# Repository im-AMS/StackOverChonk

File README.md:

# References

- [custom ergogen-footprints](https://github.com/ceoloide/ergogen-footprints)
- [3d models to view in kicad](https://github.com/joe-scotto/scottokeebs/tree/main/Extras/ScottoKicad)
- [josukey](https://github.com/Narkoleptika/josukey)
- [avocado](https://github.com/auryn31/avocado)
- [supermini pinout specs](https://docs.nordicsemi.com/bundle/ps_nrf52840/page/pin.html)
- [Arduino Pro Micro Pinout](https://cdn.sparkfun.com/assets/9/c/3/c/4/523a1765757b7f5c6e8b4567.png)
- [ergogen configs from Corney-island](https://github.com/ceoloide/corney-island/blob/main/ergogen/config.yaml)
- [svg to points](https://shinao.github.io/PathToPoints/)

# Renders

# Personal Notes and Todos
For RGB Underglow, ZMK docs recomments using high speed gpio pins. refer to the attached pinout specs above.

Try to reserve pins like so (pins in arduino format)
- D2 & D3 for I2C - for Displays
- D6 for high speed comms like RGB underglow, because docs is also using it
- D14, D15, D16 - SPI - idk what i might use this for, just leave em blank

can the battery be connected to RAW for charging or do i have to connect it to top two pins

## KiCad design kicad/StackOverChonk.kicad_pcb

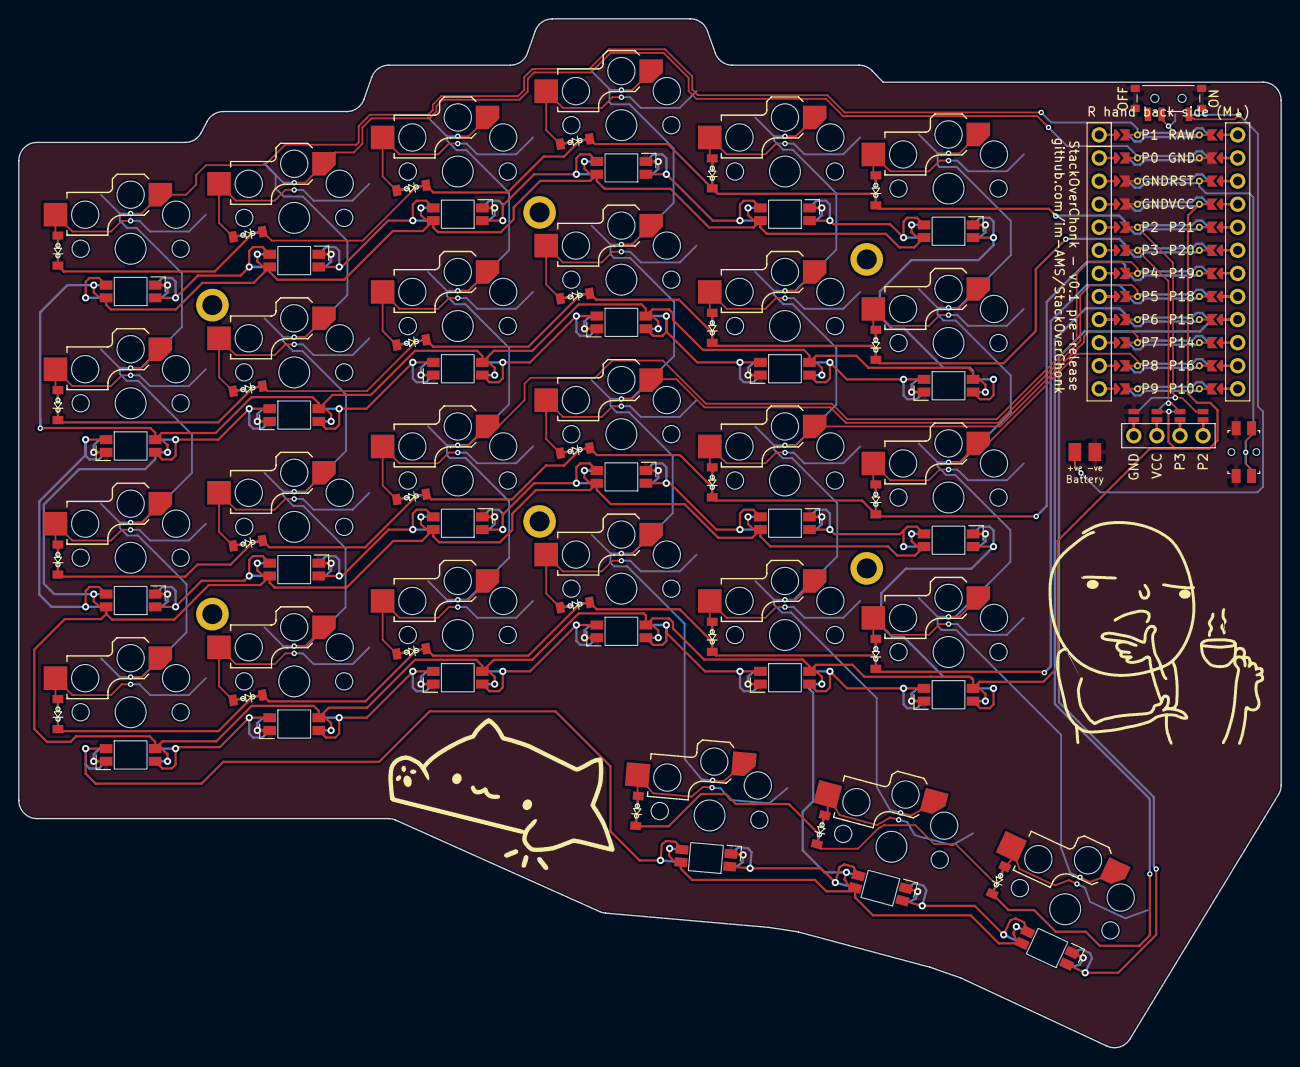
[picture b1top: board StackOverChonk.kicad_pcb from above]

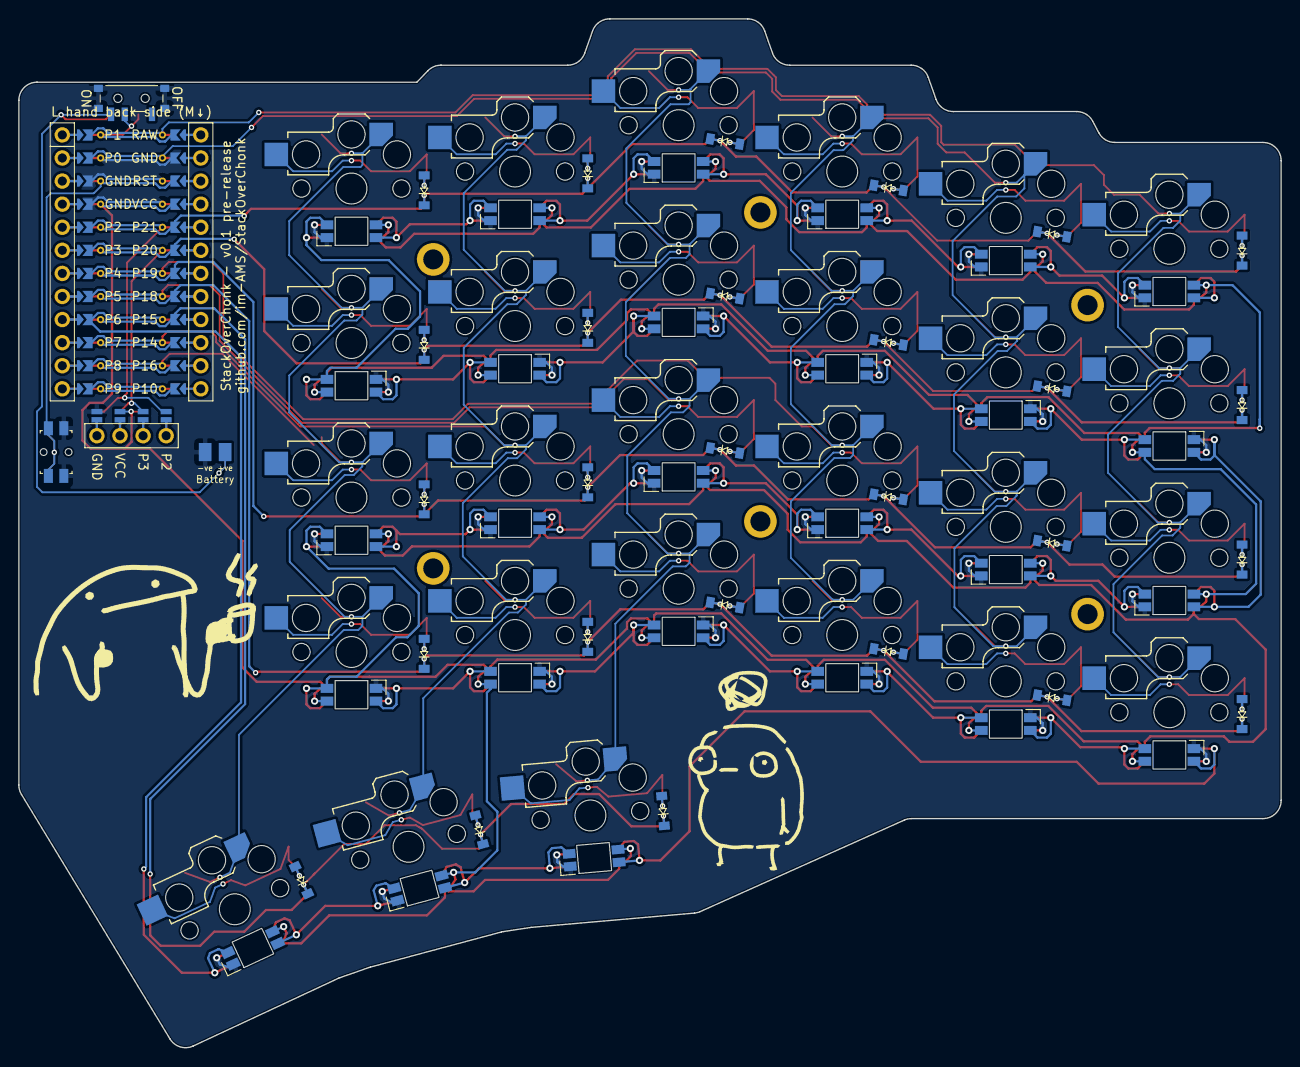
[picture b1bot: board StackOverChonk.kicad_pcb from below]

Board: 2 copper layers, 138.9 x 113.2 mm, 93 parts (35 on the bottom side), 76 nets.

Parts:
BT1, BT2: Battery_pads
D1, D2, D3, D4, D5, D6, D7, D8, D9, D10, D11, D12, D13, D14, D15, D16, D17, D18, D19, D20, D21, D22, D23, D24, D25, D26, D27: diode_tht_sod123
DISP1: display_ssd1306
H1, H2, H3, H4, H5, H6: mounting_hole_plated
LED1, LED2, LED3, LED4, LED5, LED6, LED7, LED8, LED9, LED10, LED11, LED12, LED13, LED14, LED15, LED16, LED17, LED18, LED19, LED20, LED21, LED22, LED23, LED24, LED25, LED26, LED27: led_SK6812mini-e (per-key, reversible)
MCU1: mcu_supermini_nrf52840
PWR1: power_switch_smd_side
RST1: reset_switch_smd_side
S1, S2, S3, S4, S5, S6, S7, S8, S9, S10, S11, S12, S13, S14, S15, S16, S17, S18, S19, S20, S21, S22, S23, S24, S25, S26, S27: switch_choc_v1_v2

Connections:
DISP1_1: DISP1.1, DISP1.10, DISP1.23
DISP1_2: DISP1.2, DISP1.11, DISP1.22
DISP1_3: DISP1.3, DISP1.12, DISP1.21
DISP1_4: DISP1.4, DISP1.13, DISP1.20
GND: BT1.2, BT2.2, DISP1.14, DISP1.24, LED1.3, LED2.3, LED3.3, LED4.3, LED5.3, LED6.3, LED7.3, LED8.3, LED9.3, LED10.3, LED11.3, LED12.3, LED13.3, LED14.3, LED15.3, LED16.3, LED17.3, LED18.3, LED19.3, LED20.3, LED21.3, LED22.3, LED23.3, LED24.3, LED25.3, LED26.3, LED27.3, MCU1.102, MCU1.121, MCU1.122, PWR1.STAB1, PWR1.STAB2, PWR1.STAB3, PWR1.STAB4, RST1.2, RST1.4
LED_1: LED26.4, LED27.2
LED_2: LED25.4, LED26.2
LED_3: LED1.4, LED25.2
LED_4: LED1.2, LED3.4
LED_5: LED3.2, LED5.4
LED_6: LED5.2, LED7.4
LED_7: LED7.2, LED9.4
LED_8: LED9.2, LED11.4
LED_9: LED11.2, LED23.4
LED_10: LED21.4, LED23.2
LED_11: LED19.4, LED21.2
LED_12: LED17.4, LED19.2
LED_13: LED15.4, LED17.2
LED_14: LED13.4, LED15.2
LED_15: LED2.4, LED13.2
LED_16: LED2.2, LED4.4
LED_17: LED4.2, LED6.4
LED_18: LED6.2, LED8.4
LED_19: LED8.2, LED10.4
LED_20: LED10.2, LED12.4
LED_21: LED12.2, LED24.4
LED_22: LED22.4, LED24.2
LED_23: LED20.4, LED22.2
LED_24: LED18.4, LED20.2
LED_25: LED16.4, LED18.2
LED_26: LED14.4, LED16.2
P0: MCU1.123, S5.1, S6.1, S7.1, S8.1
P1: MCU1.124, S1.1, S2.1, S3.1, S4.1
P2: DISP1.17, DISP1.27, MCU1.120
P3: DISP1.16, DISP1.26, MCU1.119
P4: MCU1.118, S9.1, S10.1, S11.1, S12.1
P5: MCU1.117, S13.1, S14.1, S15.1, S16.1, S25.1
P6: LED27.4, MCU1.116
P7: MCU1.115, S17.1, S18.1, S19.1, S20.1, S26.1
P8: MCU1.114, S21.1, S22.1, S23.1, S24.1, S27.1
P15: D25.1, D26.1, D27.1, MCU1.109
P18: D1.1, D5.1, D9.1, D13.1, D17.1, D21.1, MCU1.108
P19: D2.1, D6.1, D10.1, D14.1, D18.1, D22.1, MCU1.107
P20: D3.1, D7.1, D11.1, D15.1, D19.1, D23.1, MCU1.106
P21: D4.1, D8.1, D12.1, D16.1, D20.1, D24.1, MCU1.105
RAW: MCU1.101, PWR1.2
RST: MCU1.103, RST1.1, RST1.3
VCC: DISP1.15, DISP1.25, LED1.1, LED2.1, LED3.1, LED4.1, LED5.1, LED6.1, LED7.1, LED8.1, LED9.1, LED10.1, LED11.1, LED12.1, LED13.1, LED14.1, LED15.1, LED16.1, LED17.1, LED18.1, LED19.1, LED20.1, LED21.1, LED22.1, LED23.1, LED24.1, LED25.1, LED26.1, LED27.1, MCU1.104
matrix_index_down: D17.2, S17.2
matrix_index_home: D18.2, S18.2
matrix_index_num: D20.2, S20.2
matrix_index_up: D19.2, S19.2
matrix_inner_down: D21.2, S21.2
matrix_inner_home: D22.2, S22.2
matrix_inner_num: D24.2, S24.2
matrix_inner_up: D23.2, S23.2
matrix_middle_down: D13.2, S13.2
matrix_middle_home: D14.2, S14.2
matrix_middle_num: D16.2, S16.2
matrix_middle_up: D15.2, S15.2
matrix_outer_down: D1.2, S1.2
matrix_outer_home: D2.2, S2.2
matrix_outer_num: D4.2, S4.2
matrix_outer_up: D3.2, S3.2
matrix_pinky_down: D5.2, S5.2
matrix_pinky_home: D6.2, S6.2
matrix_pinky_num: D8.2, S8.2
matrix_pinky_up: D7.2, S7.2
matrix_ring_down: D9.2, S9.2
matrix_ring_home: D10.2, S10.2
matrix_ring_num: D12.2, S12.2
matrix_ring_up: D11.2, S11.2
pos: BT1.1, BT2.1, PWR1.1, PWR1.3
thumbs_col1_cluster: D25.2, S25.2
thumbs_col2_cluster: D26.2, S26.2
thumbs_col3_cluster: D27.2, S27.2

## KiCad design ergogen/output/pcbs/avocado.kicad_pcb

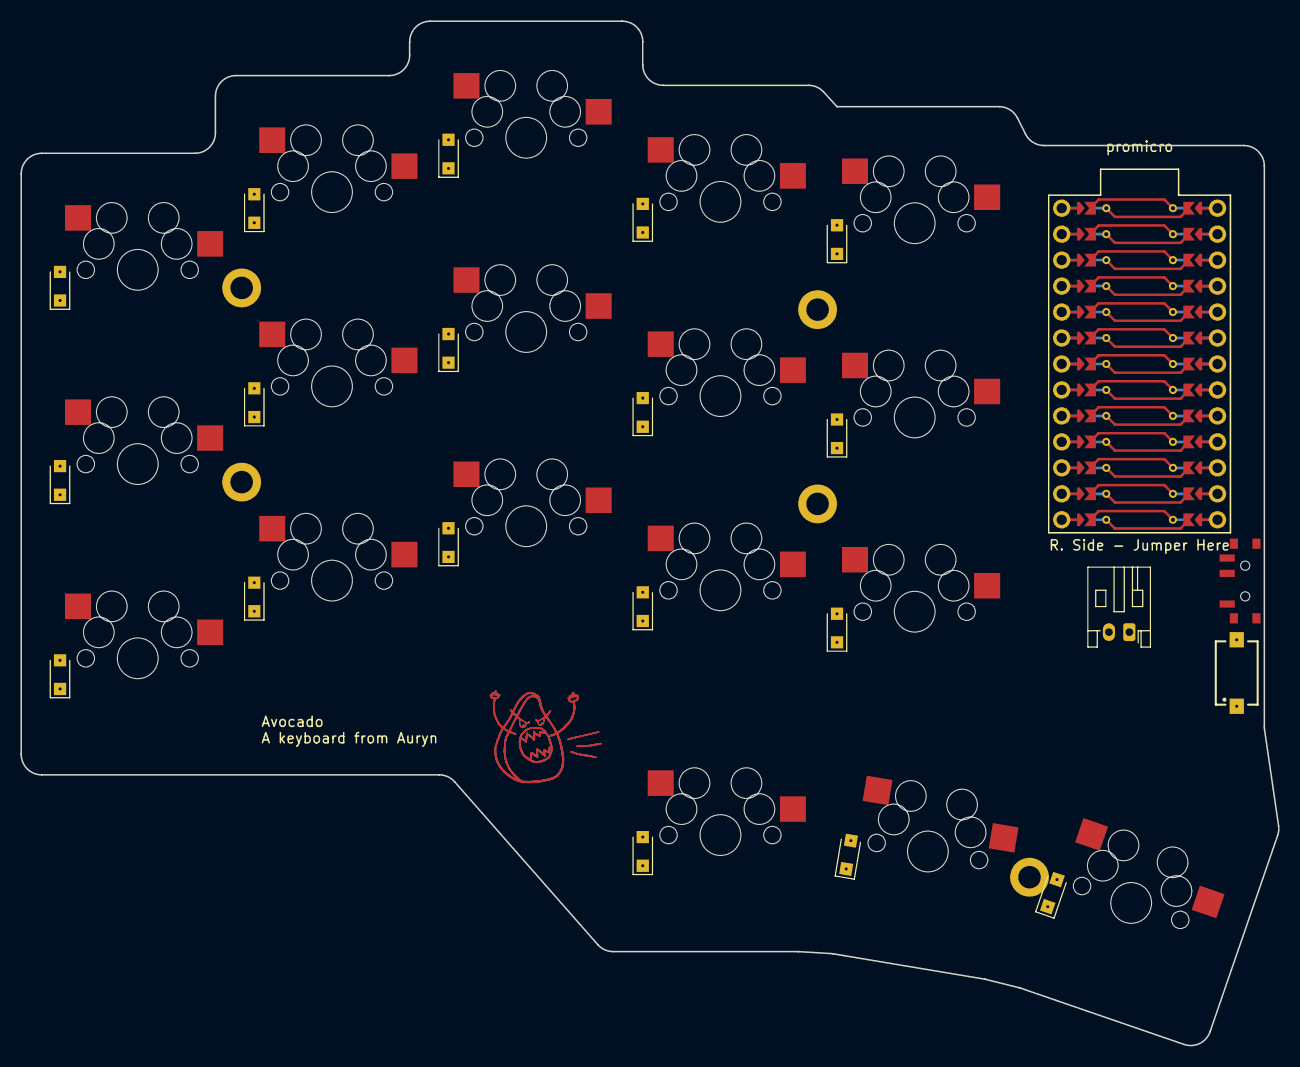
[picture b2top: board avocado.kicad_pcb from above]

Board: 2 copper layers, 123.0 x 100.2 mm, 44 parts (0 on the bottom side), 10 nets.

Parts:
D1, D2, D3, D4, D5, D6, D7, D8, D9, D10, D11, D12, D13, D14, D15, D16, D17, D18: Nexperia_CFP3_SOD-123W
H1, H2, H3, H4, H5: mounting_hole
S1, S2, S3, S4, S5, S6, S7, S8, S9, S10, S11, S12, S13, S14, S15, S16, S17, S18: MX
S19: 434121025816
T1: SW_SPDT_PCM12
_2: JST_PH_S2B-PH-K_1x02_P2.00mm_Horizontal

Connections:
P0: D2.1, D2.2, D5.1, D5.2, D8.1, D8.2, D11.1, D11.2, D14.1, D14.2, S2.2, S5.2, S8.2, S11.2, S14.2
P1: D3.1, D3.2, D6.1, D6.2, D9.1, D9.2, D12.1, D12.2, D15.1, D15.2, S3.2, S6.2, S9.2, S12.2, S15.2
P2: D1.1, D1.2, D4.1, D4.2, D7.1, D7.2, D10.1, D10.2, D13.1, D13.2, S1.2, S4.2, S7.2, S10.2, S13.2
P3: S13.1, S14.1, S15.1, S18.1
P4: S10.1, S11.1, S12.1, S17.1
P5: S7.1, S8.1, S9.1, S16.1
P6: S4.1, S5.1, S6.1
P7: S1.1, S2.1, S3.1
P8: D16.1, D16.2, D17.1, D17.2, D18.1, D18.2, S16.2, S17.2, S18.2
pos: T1.1, _2.1

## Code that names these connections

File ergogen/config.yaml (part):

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        -  ref: matrix_outer_num
           shift: [0.4kx, 0.6ky+outer_boundary]

        -  ref: matrix_pinky_num
           shift: [-0.5kx, 0.6ky+outer_boundary]
        -  ref: matrix_pinky_num
           shift: [0.4kx, 0.6ky+outer_boundary]

        -  ref: matrix_ring_num
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    - what: circle
      radius: 1.1
      where:
        ref: matrix_pinky_num
        shift: [(-kx/2), (-ky/2) -1.1]

  _hole_bottom_left:
    - what: circle
      radius: 1.1
      where:
        ref: matrix_pinky_home
        shift: [(-kx/2), (-ky/2) -1.1]

  _hole_top_right:
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    mounting_hole_top_left:
      $extends: pcbs.StackOverChonk.footprints.mounting_hole_definition
      where:
        ref: matrix_pinky_num
        shift: [(-kx/2), (-ky/2) -1.1 ]

    mounting_hole_bottom_left:
      $extends: pcbs.StackOverChonk.footprints.mounting_hole_definition
      where:
        ref: matrix_pinky_home
        shift: [(-kx/2), (-ky/2) -1.1 ]


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    pussy_cat:
      what: memes/pussy_cat
      where:
        ref: matrix_pinky_down
        shift: [8, -4]
      params:
        layer: 'F.SilkS'
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
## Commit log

2024-11-30 Initial working commit with Avocado config
2024-11-30 I dont wanna loose what i have built so far. so take a commit.
2024-12-01 added rgb leds!!
2024-12-15 I think this shit works not, lots of improvements and changes
2024-12-16 added meme characters on slikscreen
2024-12-16 ft. StackOverChonk
2024-12-16 fixed cluster pins
2024-12-17 fix diode positoning and multiple others
2024-12-20 some fixes and name pcbname changes
2024-12-20 hole fixes
2024-12-22 some changes to diode and hole placement - should fix the unconnected GND plane islanding
2024-12-22 PCB Routed
2025-01-18 First test configs setup - i have no clue if this will work
2025-01-18 Changed the case of file names
2025-01-18 Some more changes
2025-01-18 change again
2025-01-18 Ahhhhh forgot the semicolon
2025-01-18 this was not there in sofle files - so comment this out for now
2025-01-18 this is requred for the online keymap editor
2025-01-19 Some more changes and trying to check if oled and leds work
2025-01-19 try and fix1
2025-01-19 Change 2
2025-01-19 change 3 - attempt to fix the mismatch thumb keys
2025-01-19 change -4 usb debug enable
2025-01-19 change 4a - retry usb debug
2025-01-19 change 4c - try another log mode
2025-01-19 change 4d - pin 0 and 1 are tx and rx, if we disable it it shuuld work no?
2025-01-19 change 4e - lets try alternate approach
2025-01-19 change 4f - another try
2025-01-19 change 4f- again
2025-01-19 change 4g - changing the i2c pins to the oled connected pins
2025-01-19 change 4h - try to assign to other unused pins and see if it works
2025-01-19 change 4h - retry
2025-01-19 change 4i - use the nrf keymapping instead of arduino one
2025-01-19 change 4i
2025-01-19 change 5 - just remove all oled and led and debug only the columns
2025-01-19 Change 5
2025-01-19 change 5a - define pin 0 and 1 as gpio
2025-01-19 change 5a
2025-01-19 change 6: try to fix right half mirror
2025-01-19 change 6: try again
2025-01-19 change 6: try again - i think this is the last time
2025-01-20 change 7 test: debug the pins
2025-01-25 change 8: lets try to use different pin for the non working microcontroller
2025-01-25 Change 8 - i think this should work now
2025-01-25 Testing some basic config with online keymap editor
2025-01-25 trying to enable oled
2025-01-25 these are supposed to be nrf pinout formats
2025-01-25 trying to enable rgb
2025-01-25 try enable rgb again
2025-01-25 try again
2025-01-25 again
2025-01-25 rgb again
2025-01-25 custom keymappings
2025-01-25 few more custom keymappings
2025-01-25 some forgotten <> fix
2025-01-25 rgb try again
2025-01-25 lets try to enable spi debugging
2025-01-25 aahah
2025-01-25 lets try to enable only rgb leds now
2025-01-25 some new keymaps and key fixes
2025-01-25 swap the controls
2025-01-25 ahhhhhh should have rechecked the files before commit
2025-01-25 some more improvements
2025-01-25 error fixes
2025-01-25 damn claude forgot to add brackets
2025-01-25 some more fine tuning
2025-01-25 lets enable zmk studio
2025-01-27 some more tweeks to keymap
2025-01-27 may be this should fix the build errors?
2025-01-27 nah just remove this
2025-01-28 claude effed up again, i had to correct the code, also added num pad now
2025-01-28 ahhh duplicate names fix
2025-01-28 ahh fix the typo
2025-01-28 why am i dumb!?
2025-01-28 May be i should stop relying on LLMs altogeather
2025-01-28 this should solve connecting via bt when powering through usb power
2025-01-28 ahh forgot to import the header file for this to work!
2025-02-01 remove all oled related configs for now, and just focus on rgb for a sec
2025-02-01 Finally RGBs are working!!, made some adjustments now
2025-02-01 Some more fine tunings
2025-02-02 Lets try to add oled display now
2025-02-02 remove this usb logging
2025-02-02 lets try adding this and see if it helps - found this from the lilly configs
2025-02-02 ahh i see i forgot to uncomment this line
2025-02-02 added the holes location in dxf file
2025-02-11 lets try to see if i can get oleds working with this
2025-07-20 backspace key and space layer behaviour changes
2025-07-20 some more finetuning
2025-07-20 some more changes and finetuning
2025-07-20 layer change individually for each half
2025-07-20 ft homerow mods
2025-10-06 some customizations
2025-10-06 fixed some redefinition issues
2025-10-06 rgb keys gpt errors keymap
2025-10-06 fixed manual error
2025-10-06 fixing gpt errors again
2025-10-06 fixing issues for undefined macro
2025-10-06 label is deprecated here apparently - removed it
2025-10-06 fix error, binding cells has to be 2 not 0 for hold tap
2025-10-06 trying to fix that same error again
2025-10-06 layer error fixed for esc_hyper
2025-10-06 Some fine tuning
2025-10-06 bug fix and bck spc and ctrl mapping
2025-10-06 fine tuning and fixes
2025-10-06 changed tapdance duration for cmd cmd spc
2025-10-06 finetuning td
2025-10-11 fine tuning thumb delays
2025-10-30 some latency tweaks
2025-11-26 slight increase in debounce
2025-12-01 removing display and increase bt responsiveness
2025-12-01 moving comments around
2025-12-01 cannot set this value below 6
2025-12-01 some changes
2025-12-10 setting zmk version as 0.3
2025-12-10 explicity disconnect other bt profiles
2025-12-10 changing the order
2025-12-10 trying a different approach
2025-12-10 fixing a dumb mistake
2025-12-11 trying to set this now
2026-01-15 ft: Local build setup with docker
2026-01-15 docs
2026-02-08 temp commit
2026-02-09 Intermediate commit, logs enabled
